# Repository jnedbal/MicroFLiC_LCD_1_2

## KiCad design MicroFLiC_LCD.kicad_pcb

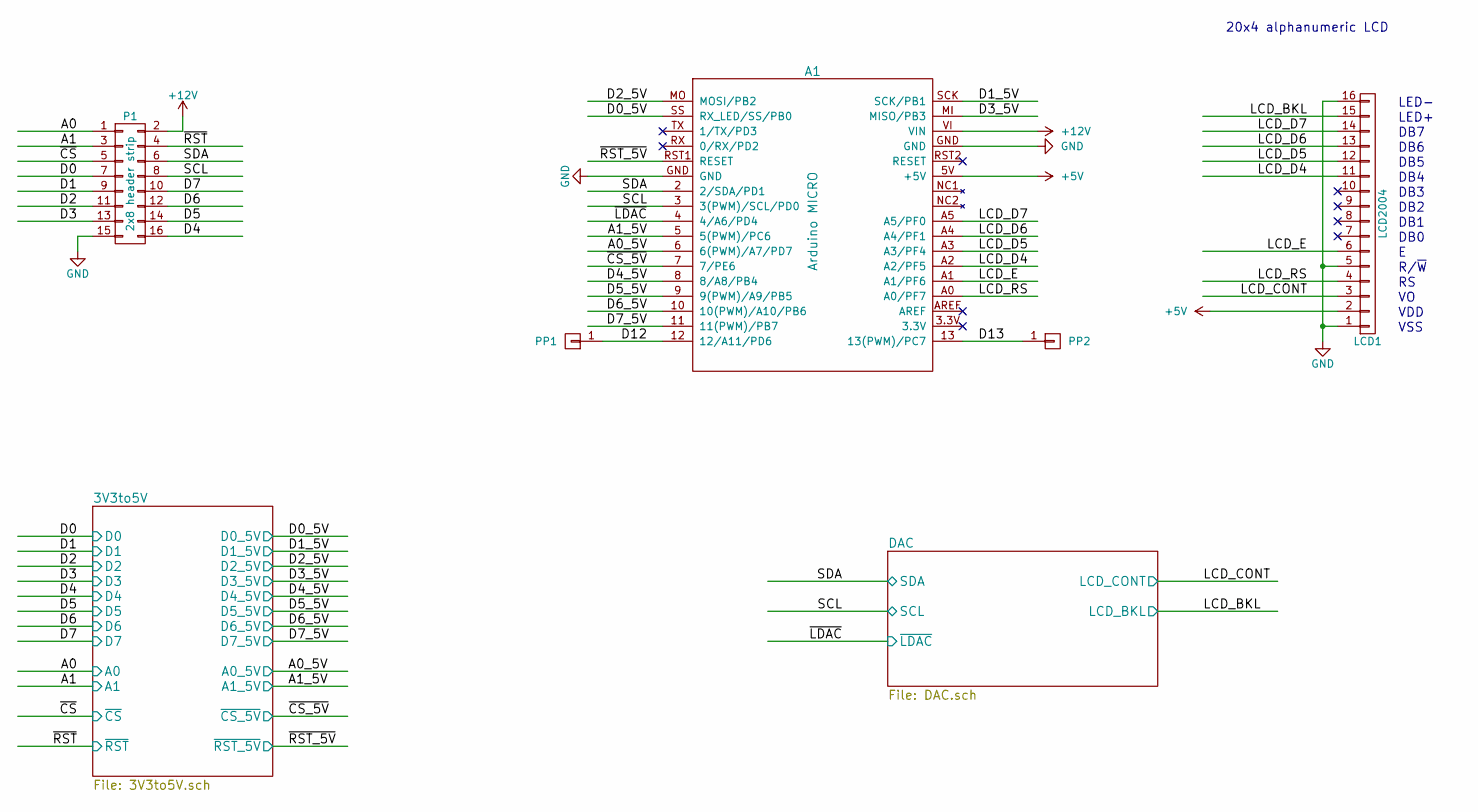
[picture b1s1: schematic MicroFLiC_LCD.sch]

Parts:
A1: Arduino MICRO; ArduinoMicro; Part Number A000053
LCD1: LCD2004; Part Number MC42005A12W-VNMLR
P1: 2x8 header strip; Pin_Header_Straight_2x08; Part Number M20-9980845
PP1, PP2: CONN_01X01; PIN_ARRAY_1

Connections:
+5V: A1.5V (+5V), LCD1.2; also elsewhere on the board
+12V: A1.VI (VIN), P1.2; also elsewhere on the board
/3V3to5V/A0: P1.1; also elsewhere on the board
/3V3to5V/A0_5V: A1.6 (6(PWM)/A7/PD7); also elsewhere on the board
/3V3to5V/A1: P1.3; also elsewhere on the board
/3V3to5V/A1_5V: A1.5 (5(PWM)/PC6); also elsewhere on the board
/3V3to5V/D0: P1.7; also elsewhere on the board
/3V3to5V/D0_5V: A1.SS (RX_LED/SS/PB0); also elsewhere on the board
/3V3to5V/D1: P1.9; also elsewhere on the board
/3V3to5V/D1_5V: A1.SCK (SCK/PB1); also elsewhere on the board
/3V3to5V/D2: P1.11; also elsewhere on the board
/3V3to5V/D2_5V: A1.MO (MOSI/PB2); also elsewhere on the board
/3V3to5V/D3: P1.13; also elsewhere on the board
/3V3to5V/D3_5V: A1.MI (MISO/PB3); also elsewhere on the board
/3V3to5V/D4: P1.16; also elsewhere on the board
/3V3to5V/D4_5V: A1.8 (8/A8/PB4); also elsewhere on the board
/3V3to5V/D5: P1.14; also elsewhere on the board
/3V3to5V/D5_5V: A1.9 (9(PWM)/A9/PB5); also elsewhere on the board
/3V3to5V/D6: P1.12; also elsewhere on the board
/3V3to5V/D6_5V: A1.10 (10(PWM)/A10/PB6); also elsewhere on the board
/3V3to5V/D7: P1.10; also elsewhere on the board
/3V3to5V/D7_5V: A1.11 (11(PWM)/PB7); also elsewhere on the board
/3V3to5V/~CS: P1.5; also elsewhere on the board
/3V3to5V/~CS_5V: A1.7 (7/PE6); also elsewhere on the board
/3V3to5V/~RST: P1.4; also elsewhere on the board
/3V3to5V/~RST_5V: A1.RST1 (RESET); also elsewhere on the board
/D12: A1.12 (12/A11/PD6), PP1.1
/D13: A1.13 (13(PWM)/PC7), PP2.1
/DAC/LCD_BKL: LCD1.15; also elsewhere on the board
/DAC/LCD_CONT: LCD1.3; also elsewhere on the board
/DAC/SCL: A1.3 (3(PWM)/SCL/PD0), P1.8; also elsewhere on the board
/DAC/SDA: A1.2 (2/SDA/PD1), P1.6; also elsewhere on the board
/DAC/~LDAC: A1.4 (4/A6/PD4); also elsewhere on the board
/LCD_D4: A1.A2 (A2/PF5), LCD1.11
/LCD_D5: A1.A3 (A3/PF4), LCD1.12
/LCD_D6: A1.A4 (A4/PF1), LCD1.13
/LCD_D7: A1.A5 (A5/PF0), LCD1.14
/LCD_E: A1.A1 (A1/PF6), LCD1.6
/LCD_RS: A1.A0 (A0/PF7), LCD1.4
GND: A1.GND, LCD1.1, LCD1.5, LCD1.16, P1.15; also elsewhere on the board

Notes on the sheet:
LED-
LED+
DB7
DB6
DB5
DB4
DB3
DB2
DB1
DB0
R/~W
VDD
VSS
20x4 alphanumeric LCD

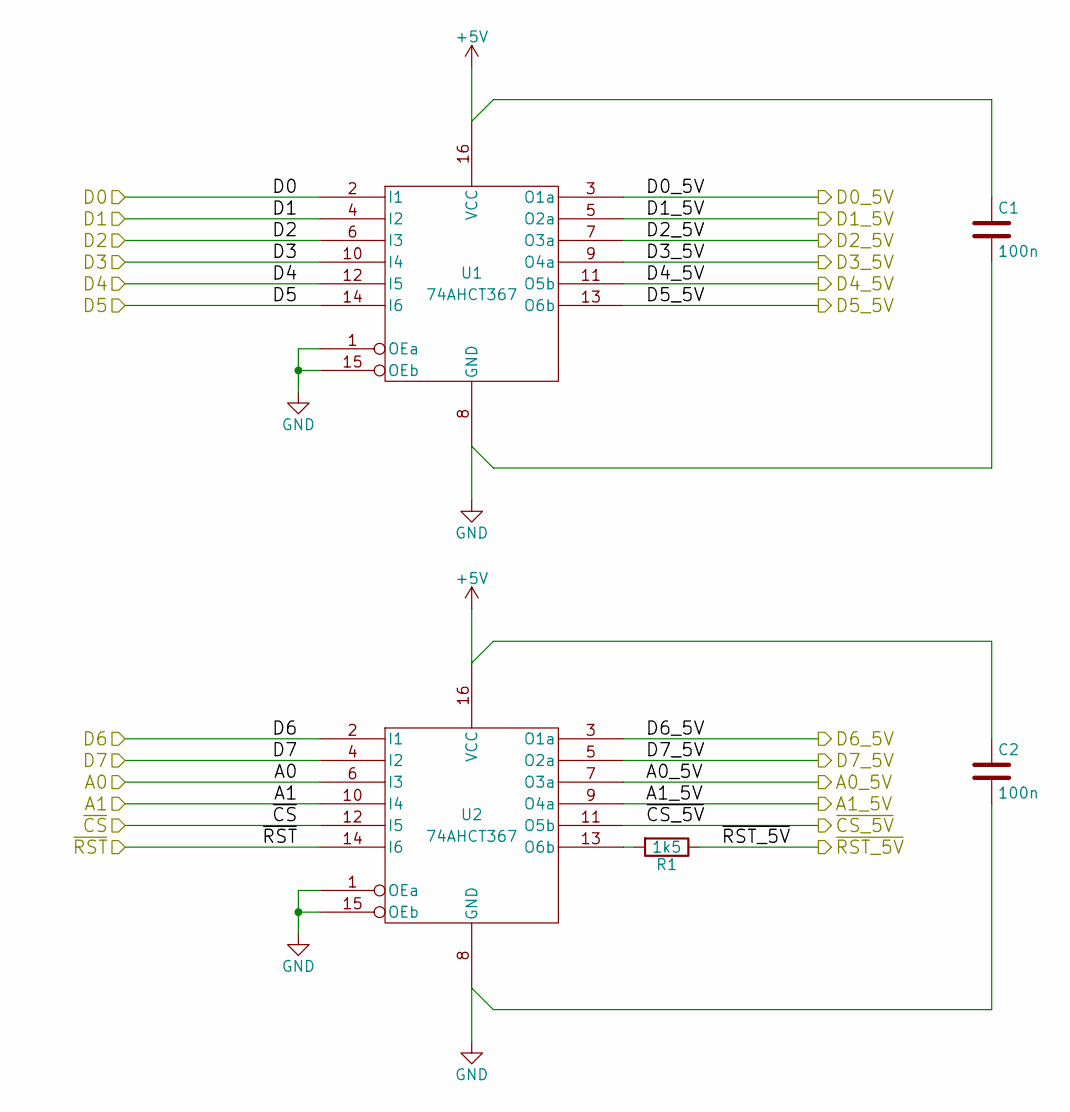
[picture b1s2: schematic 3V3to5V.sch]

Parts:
C1, C2: 100n; C_0805; Part Number MC0805B104K250CT
R1: 1k5; R_0805; Part Number MCWR08X1501FTL
U1, U2: 74AHCT367; SOIC-16_3.9x9.9mm_Pitch1.27mm; Part Number SN74AHCT367D

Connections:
+5V: C1.1, C2.1, U1.16 (VCC), U2.16 (VCC); also elsewhere on the board
/3V3to5V/A0: U2.6 (I3); also elsewhere on the board
/3V3to5V/A0_5V: U2.7 (O3a); also elsewhere on the board
/3V3to5V/A1: U2.10 (I4); also elsewhere on the board
/3V3to5V/A1_5V: U2.9 (O4a); also elsewhere on the board
/3V3to5V/D0: U1.2 (I1); also elsewhere on the board
/3V3to5V/D0_5V: U1.3 (O1a); also elsewhere on the board
/3V3to5V/D1: U1.4 (I2); also elsewhere on the board
/3V3to5V/D1_5V: U1.5 (O2a); also elsewhere on the board
/3V3to5V/D2: U1.6 (I3); also elsewhere on the board
/3V3to5V/D2_5V: U1.7 (O3a); also elsewhere on the board
/3V3to5V/D3: U1.10 (I4); also elsewhere on the board
/3V3to5V/D3_5V: U1.9 (O4a); also elsewhere on the board
/3V3to5V/D4: U1.12 (I5); also elsewhere on the board
/3V3to5V/D4_5V: U1.11 (O5b); also elsewhere on the board
/3V3to5V/D5: U1.14 (I6); also elsewhere on the board
/3V3to5V/D5_5V: U1.13 (O6b); also elsewhere on the board
/3V3to5V/D6: U2.2 (I1); also elsewhere on the board
/3V3to5V/D6_5V: U2.3 (O1a); also elsewhere on the board
/3V3to5V/D7: U2.4 (I2); also elsewhere on the board
/3V3to5V/D7_5V: U2.5 (O2a); also elsewhere on the board
/3V3to5V/~CS: U2.12 (I5); also elsewhere on the board
/3V3to5V/~CS_5V: U2.11 (O5b); also elsewhere on the board
/3V3to5V/~RST: U2.14 (I6); also elsewhere on the board
/3V3to5V/~RST_5V: R1.1; also elsewhere on the board
GND: C1.2, C2.2, U1.1 (OEa), U1.8 (GND), U1.15 (OEb), U2.1 (OEa), U2.8 (GND), U2.15 (OEb); also elsewhere on the board
unnamed: R1.2, U2.13 (O6b)

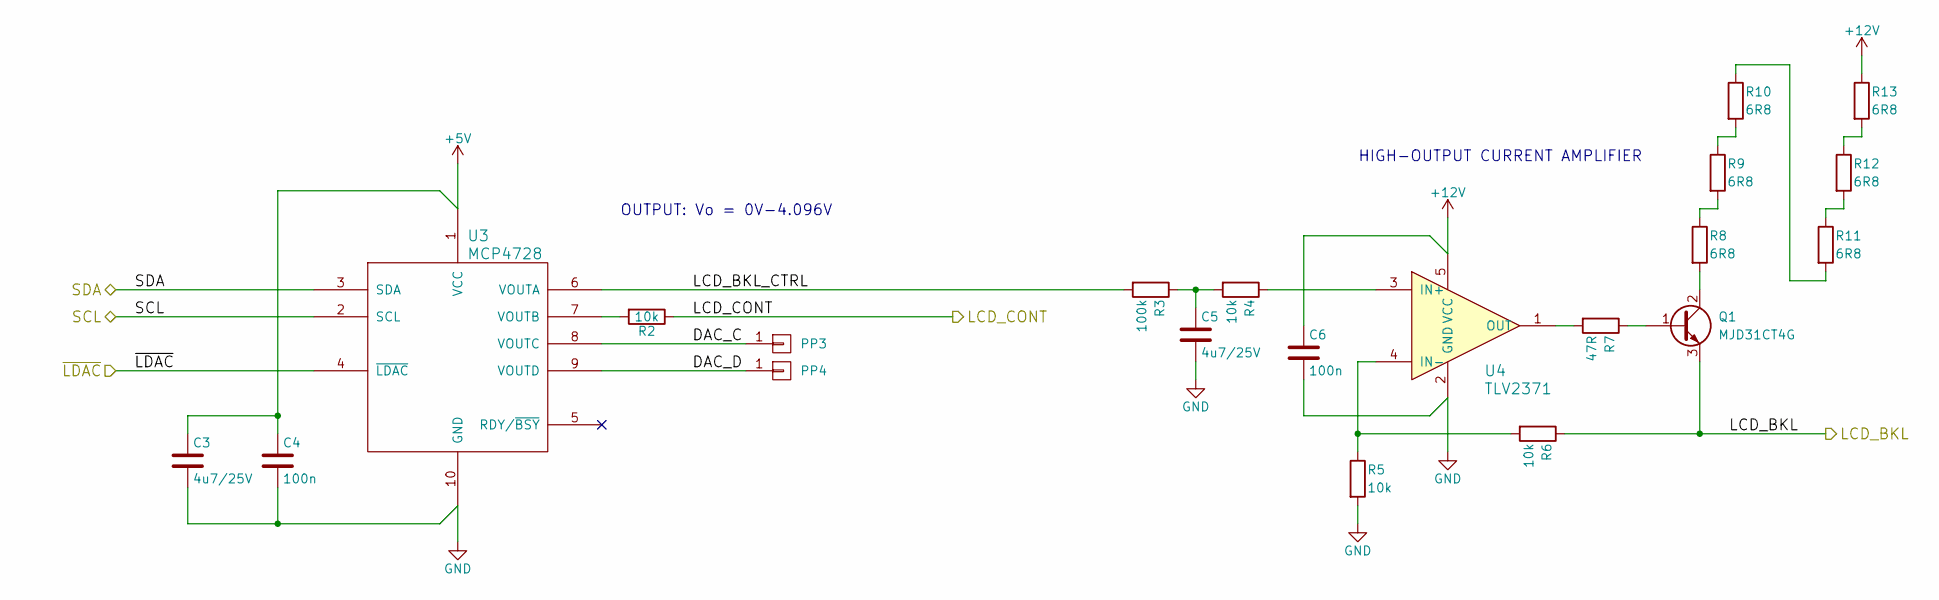
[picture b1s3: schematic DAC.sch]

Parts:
C3, C5: 4u7/25V; C_0805; Part Number GRM21BR61E475MA12L
C4, C6: 100n; C_0805; Part Number MC0805B104K250CT
PP3, PP4: CONN_01X01; PIN_ARRAY_1
Q1: MJD31CT4G; TO-252-2Lead; Part Number MJD31CT4G
R2, R4, R5, R6: 10k; R_0805; Part Number MCMR08X1002FTL
R3: 100k; R_0805; Part Number MCWR08X1003FTL
R7: 47R; R_0805; Part Number MCWR08X47R0FTL
R8, R9, R10, R11, R12, R13: 6R8; R_0805; Part Number MCWR08W6R80FTL
U3: MCP4728; MSOP-10_3x3mm_Pitch0.5mm; Part Number MCP4728-E/UN
U4: TLV2371; SOT-23-5; Part Number TLV2371IDBVT

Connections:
+5V: C3.1, C4.1, U3.1 (VCC); also elsewhere on the board
+12V: C6.1, R13.1, U4.5 (VCC); also elsewhere on the board
/DAC/DAC_C: PP3.1, U3.8 (VOUTC)
/DAC/DAC_D: PP4.1, U3.9 (VOUTD)
/DAC/LCD_BKL: Q1.3 (E), R6.1; also elsewhere on the board
/DAC/LCD_BKL_CTRL: R3.2, U3.6 (VOUTA)
/DAC/LCD_CONT: R2.1; also elsewhere on the board
/DAC/SCL: U3.2 (SCL); also elsewhere on the board
/DAC/SDA: U3.3 (SDA); also elsewhere on the board
/DAC/~LDAC: U3.4 (~LDAC); also elsewhere on the board
GND: C3.2, C4.2, C5.2, C6.2, R5.2, U3.10 (GND), U4.2 (GND); also elsewhere on the board
unnamed: C5.1, R3.1, R4.2
unnamed: Q1.1 (B), R7.1
unnamed: Q1.2 (C), R8.2
unnamed: R2.2, U3.7 (VOUTB)
unnamed: R4.1, U4.3 (IN+)
unnamed: R5.1, R6.2, U4.4 (IN-)
unnamed: R7.2, U4.1 (OUT)
unnamed: R8.1, R9.2
unnamed: R10.1, R11.2
unnamed: R9.1, R10.2
unnamed: R11.1, R12.2
unnamed: R12.1, R13.2

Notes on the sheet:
OUTPUT: Vo = 0V-4.096V
HIGH-OUTPUT CURRENT AMPLIFIER

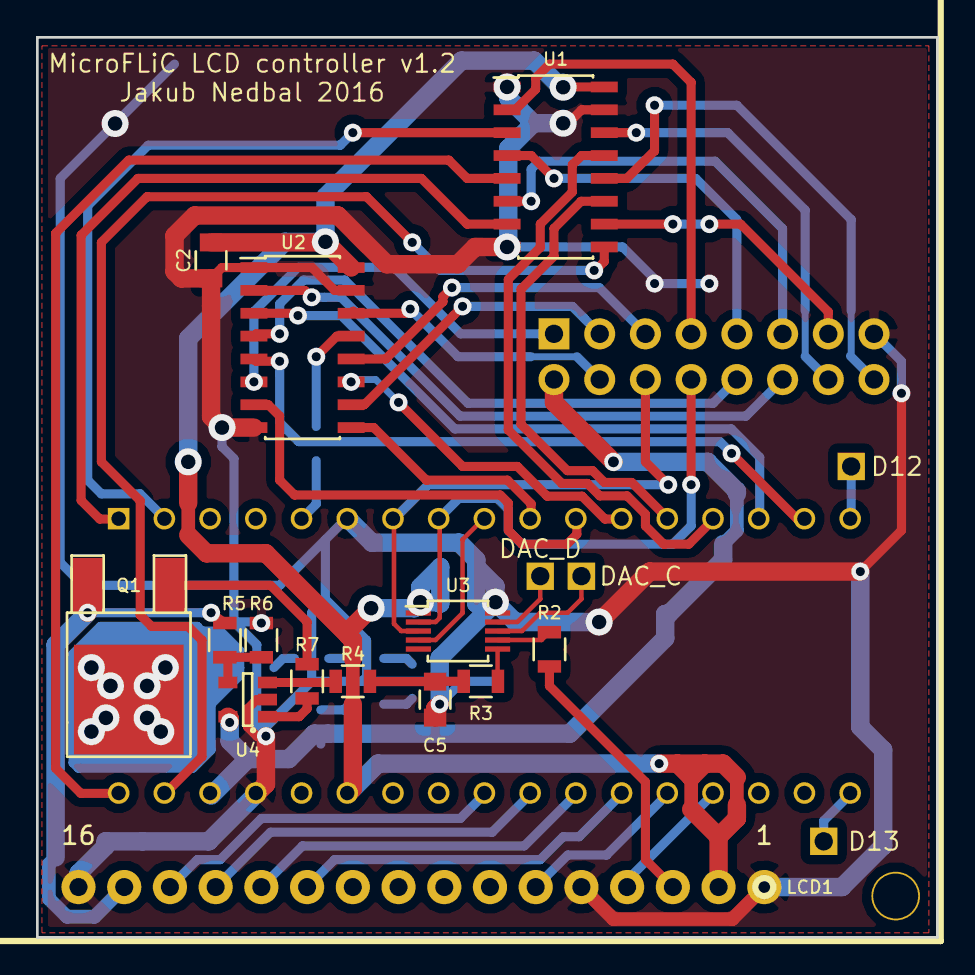
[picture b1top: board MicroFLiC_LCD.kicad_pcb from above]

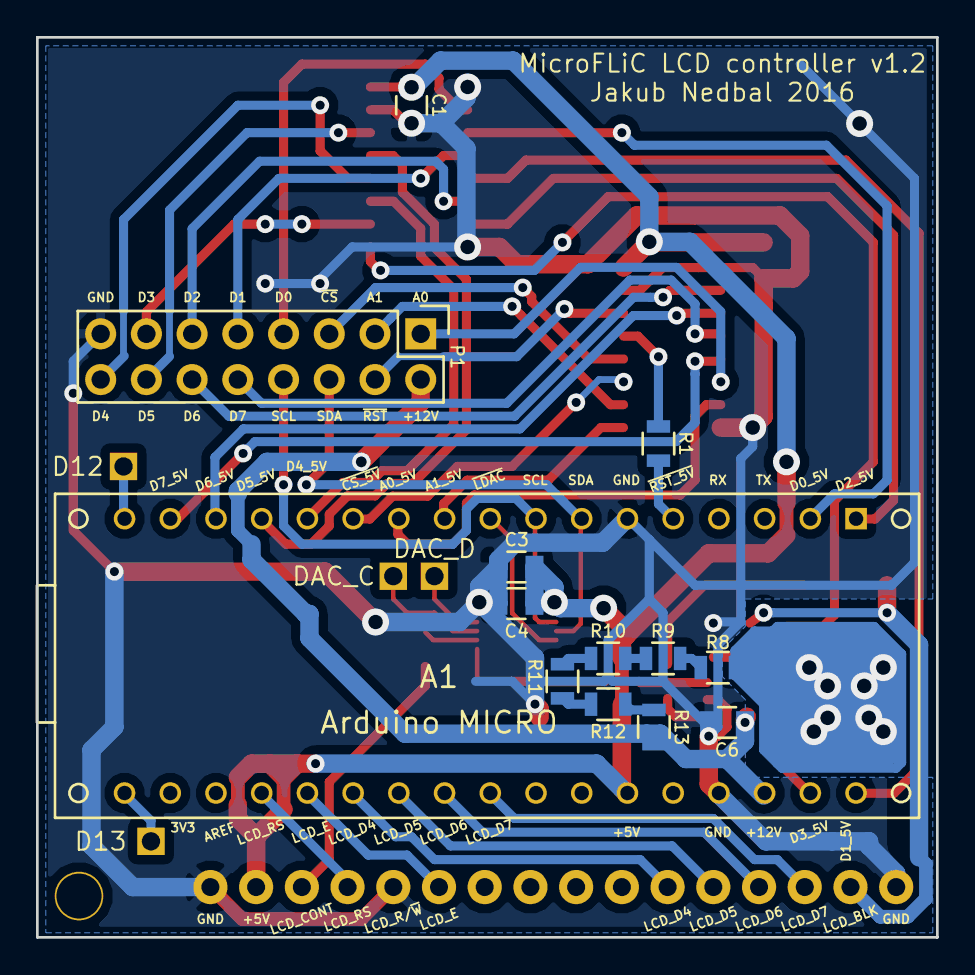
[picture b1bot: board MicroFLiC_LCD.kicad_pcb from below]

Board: 2 copper layers, 50.0 x 50.0 mm, 31 parts (13 on the bottom side), 56 nets.

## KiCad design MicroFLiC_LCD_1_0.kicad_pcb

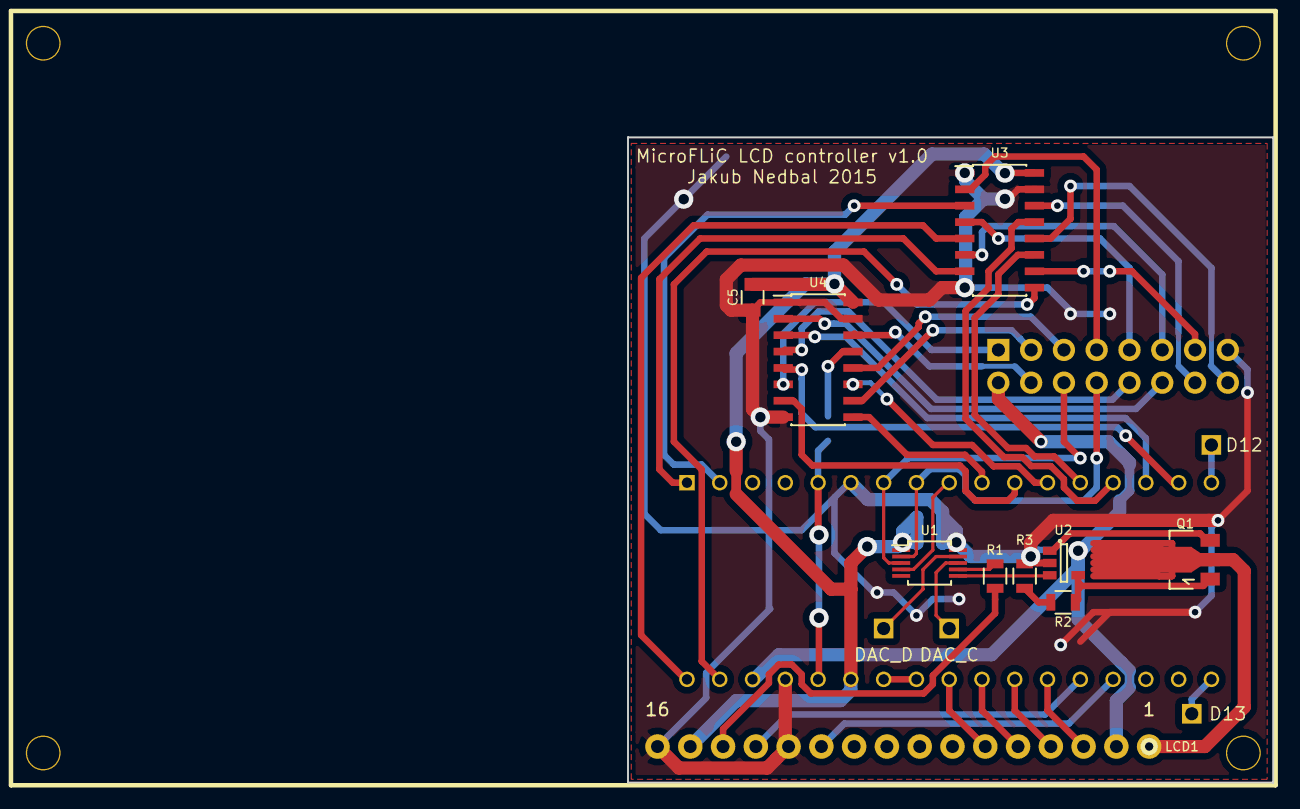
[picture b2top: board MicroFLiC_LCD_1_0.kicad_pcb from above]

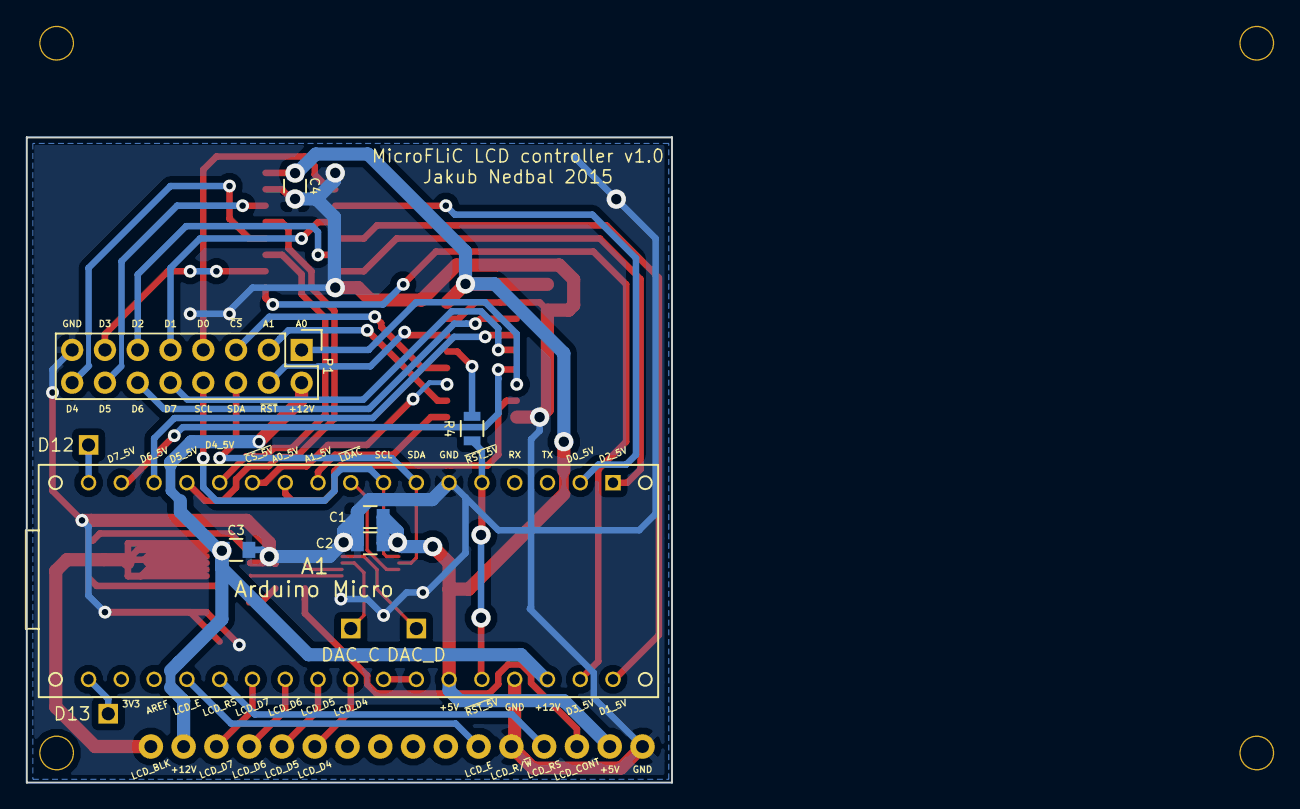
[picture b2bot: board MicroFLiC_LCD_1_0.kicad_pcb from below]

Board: 2 copper layers, 50.0 x 50.0 mm, 21 parts (7 on the bottom side), 48 nets.

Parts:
A1: Arduino Micro; ArduinoMicro
C1: 10u; C_0805
C2, C3: 100n; C_0805
C4, C5: C; C_0805
LCD1: LCD2004
P1: CONN_02X08; Pin_Header_Straight_2x08
PP1, PP2, PP3, PP4: CONN_01X01; PIN_ARRAY_1
Q1: BCX54-16; SOT89-3_Housing
R1: 10k; R_0805
R2, R3: 27R; R_0805
R4: 1K5; R_0805
U1: MCP4728; MSOP-10_3x3mm_Pitch0.5mm
U2: TLV2371; SOT-23-5
U3, U4: 74AHCT367; SOIC-16_3.9x9.9mm_Pitch1.27mm

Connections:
+5V: A1.5V, C1.1, C2.1, C4.1, C5.1, LCD1.15, U1.1, U3.16, U4.16
+12V: A1.VI, C3.1, LCD1.2, P1.2, U2.5
/3V3to5V/A0: P1.1, U4.6
/3V3to5V/A0_5V: A1.6, U4.7
/3V3to5V/A1: P1.3, U4.10
/3V3to5V/A1_5V: A1.5, U4.9
/3V3to5V/D0: P1.7, U3.2
/3V3to5V/D0_5V: A1.SS, U3.3
/3V3to5V/D1: P1.9, U3.4
/3V3to5V/D1_5V: A1.SCK, U3.5
/3V3to5V/D2: P1.11, U3.6
/3V3to5V/D2_5V: A1.MO, U3.7
/3V3to5V/D3: P1.13, U3.10
/3V3to5V/D3_5V: A1.MI, U3.9
/3V3to5V/D4: P1.16, U3.12
/3V3to5V/D4_5V: A1.8, U3.11
/3V3to5V/D5: P1.14, U3.14
/3V3to5V/D5_5V: A1.9, U3.13
/3V3to5V/D6: P1.12, U4.2
/3V3to5V/D6_5V: A1.10, U4.3
/3V3to5V/D7: P1.10, U4.4
/3V3to5V/D7_5V: A1.11, U4.5
/3V3to5V/~CS: P1.5, U4.12
/3V3to5V/~CS_5V: A1.7, U4.11
/3V3to5V/~RST: P1.4, U4.14
/3V3to5V/~RST_5V: A1.RST, R4.1
/D12: A1.12, PP1.1
/D13: A1.13, PP4.1
/DAC_C: PP2.1, U1.8
/DAC_D: PP3.1, U1.9
/LCD_BKL: LCD1.1, Q1.2
/LCD_BKL_CTRL: U1.6, U2.3
/LCD_CONT: LCD1.14, R1.1
/LCD_D4: A1.A5, LCD1.6
/LCD_D5: A1.A4, LCD1.5
/LCD_D6: A1.A3, LCD1.4
/LCD_D7: A1.A2, LCD1.3
/LCD_E: A1.A0, LCD1.11
/LCD_RS: A1.A1, LCD1.13
/SCL: A1.3, P1.8, U1.2
/SDA: A1.2, P1.6, U1.3
/~LDAC: A1.4, U1.4
GND: A1.GND, C1.2, C2.2, C3.2, C4.2, C5.2, LCD1.12, LCD1.16, P1.15, R3.2, U1.10, U2.2, U3.1, U3.8, U3.15, U4.1, U4.8, U4.15
unnamed: Q1.1, R2.1, U2.4
unnamed: Q1.3, U2.1
unnamed: R1.2, U1.7
unnamed: R2.2, R3.1
unnamed: R4.2, U4.13

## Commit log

2015-12-12 Schematics is ready
2015-12-12 Created the PCB with 3D models
2016-01-06 Final production board v1.0. Corrected LCD part v1.1
2016-02-19 Added connectors for LCD to the schematics
2016-02-26 Renamed files, added part description
2016-03-02 Fixed label of 1k5 resistor
2016-03-02 Fixed LCD part description
2016-03-18 Fixed LCD orientation, added powerful emitter-follower amplifier
2016-03-21 Changed 47R resistor part number
2016-03-23 Finalized PCB for production
2016-05-24 Fixed silk arrangement to avoid overlaps
2016-06-23 Organized the transistor label a bit.
2016-06-24 Added current-limiting resistors on the LCD backlight
2016-06-24 Changed resistors on the PCB
